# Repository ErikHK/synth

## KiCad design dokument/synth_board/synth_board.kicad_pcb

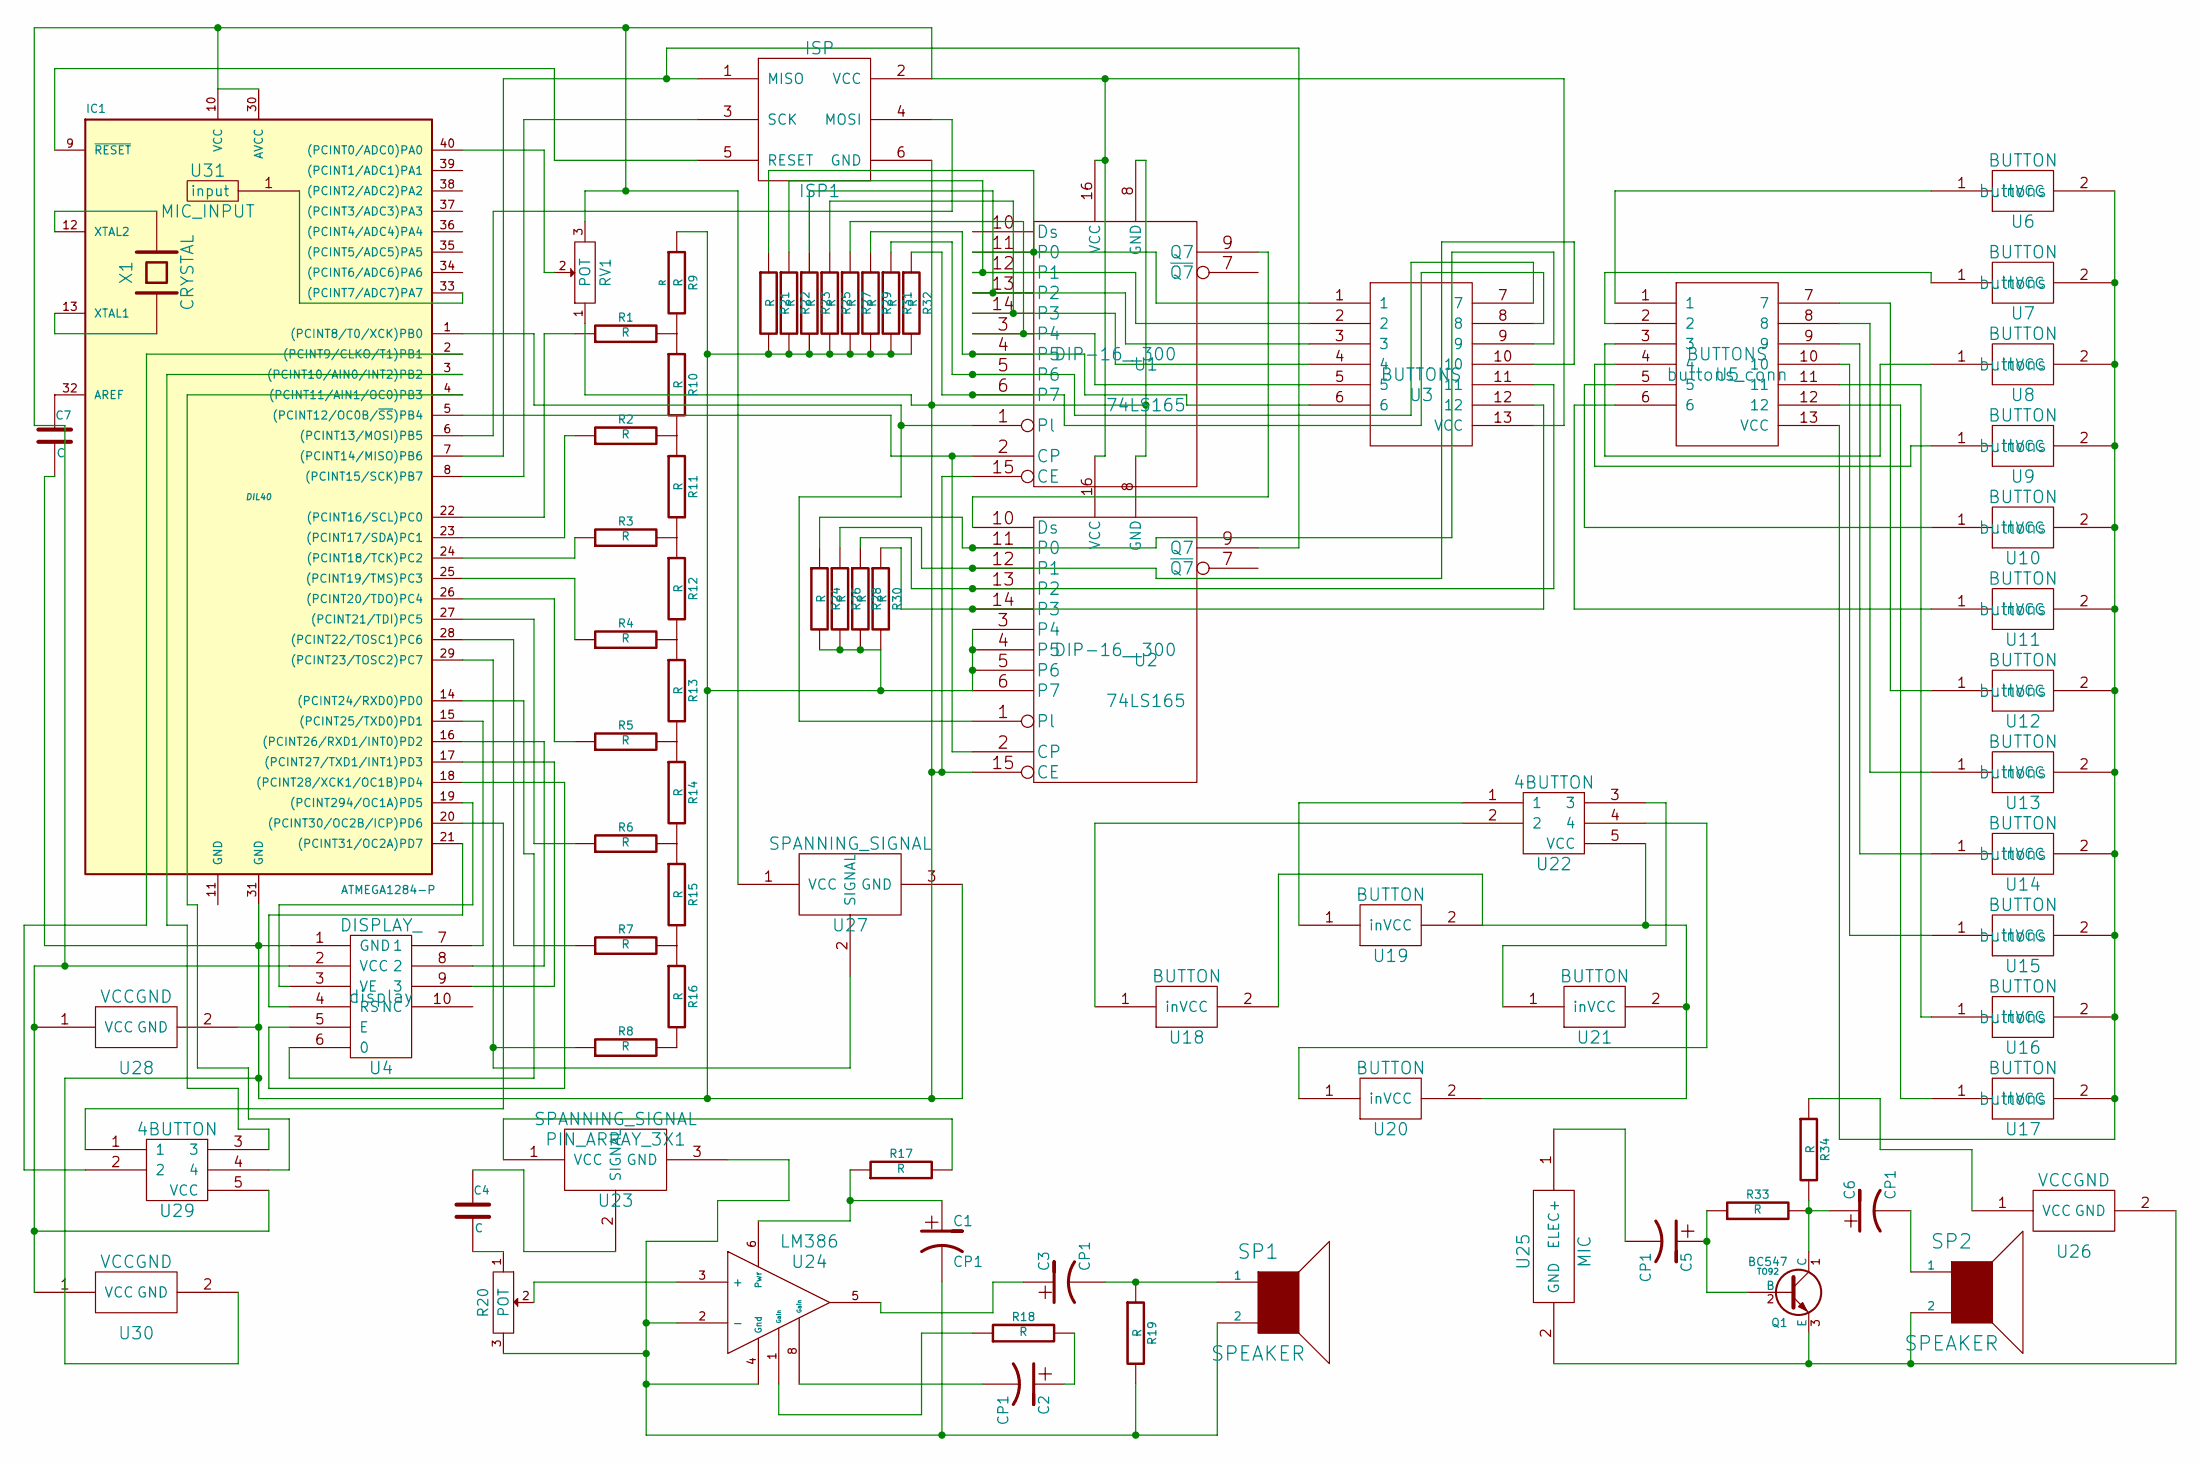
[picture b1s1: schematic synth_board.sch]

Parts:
C1, C2, C3, C5, C6: CP1
C4, C7: C
IC1: ATMEGA1284-P; DIL40
ISP1: ISP
Q1: BC547; TO92
R1, R2, R3, R4, R5, R6, R7, R8, R10, R11, R12, R13, R14, R15, R16, R17, R18, R19, R21, R22, R23, R24, R25, R26, R27, R28, R29, R30, R31, R32, R33, R34: R
R9: R
R20: POT
RV1: POT
SP1, SP2: SPEAKER
U1, U2: 74LS165; DIP-16__300
U3: BUTTONS
U4: DISPLAY_; display
U5: BUTTONS; buttons_conn
U6, U7, U8, U9, U10, U11, U12, U13, U14, U15, U16, U17: BUTTON; buttons
U18, U19, U20, U21: BUTTON
U22, U29: 4BUTTON
U23: SPANNING_SIGNAL; PIN_ARRAY_3X1
U24: LM386
U25: MIC
U26, U28, U30: VCCGND
U27: SPANNING_SIGNAL
U31: MIC_INPUT
X1: CRYSTAL

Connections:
unnamed: C4.1, U23.2 (SIGNAL)
unnamed: C4.2, R20.1
unnamed: R18.1, U24.1 (Gain)
unnamed: C2.2, U24.8 (Gain)
unnamed: C3.1, U24.5
unnamed: C2.1, R18.2
unnamed: R22.1, U1.12 (P1), U3.2
unnamed: R21.1, U1.11 (P0), U3.1
unnamed: R27.1, U1.3 (P4), U3.5
unnamed: R25.1, U1.14 (P3), U3.4
unnamed: U5.9, U14.1 (in)
unnamed: U5.5, U10.1 (in)
unnamed: U5.6, U11.1 (in)
unnamed: U5.7, U12.1 (in)
unnamed: U5.8, U13.1 (in)
unnamed: U5.10, U15.1 (in)
unnamed: U5.11, U16.1 (in)
unnamed: U5.12, U17.1 (in)
unnamed: U5.3, U8.1 (in)
unnamed: U5.2, U7.1 (in)
unnamed: U5.4, U9.1 (in)
unnamed: R20.2, U24.3 (+)
unnamed: U21.1 (in), U22.3
unnamed: C1.2, R19.2, R20.3, SP1.2, U23.3 (GND), U24.2 (-), U24.4 (Gnd)
unnamed: C1.1, R17.1, U24.6 (Pwr)
unnamed: R17.2, U23.1 (VCC)
unnamed: U19.1 (in), U22.1
unnamed: U18.1 (in), U22.2
unnamed: IC1.20 ((PCINT30/OC2B/ICP)PD6), U29.1
unnamed: IC1.13 (XTAL1), X1.1
unnamed: IC1.12 (XTAL2), X1.2
unnamed: C6.2, SP2.1
unnamed: Q1.3 (E), SP2.2, U25.2 (GND), U26.2 (GND)
unnamed: IC1.2 ((PCINT9/CLKO/T1)PB1), U29.2
unnamed: IC1.40 ((PCINT0/ADC0)PA0), RV1.2
unnamed: IC1.33 ((PCINT7/ADC7)PA7), U31.1
unnamed: IC1.3 ((PCINT10/AIN0/INT2)PB2), U29.3
unnamed: IC1.4 ((PCINT11/AIN1/OC0)PB3), U29.4
unnamed: R23.1, U1.13 (P2), U3.3
unnamed: C5.2, U25.1 (ELEC+)
unnamed: IC1.15 ((PCINT25/TXD0)PD1), U4.7 (1)
unnamed: IC1.19 ((PCINT294/OC1A)PD5), U4.3 (VE)
unnamed: U20.1 (in), U22.4
unnamed: C6.1, Q1.1 (C), R33.2, R34.2
unnamed: R34.1, U26.1 (VCC)
unnamed: IC1.21 ((PCINT31/OC2A)PD7), U4.4 (RS)
unnamed: IC1.14 ((PCINT24/RXD0)PD0), U4.6 (0)
unnamed: IC1.16 ((PCINT26/RXD1/INT0)PD2), U4.8 (2)
unnamed: IC1.17 ((PCINT27/TXD1/INT1)PD3), U4.9 (3)
unnamed: U5.1, U6.1 (in)
unnamed: IC1.5 ((PCINT12/OC0B/~SS~)PB4), U1.2 (CP), U2.2 (CP)
unnamed: R24.1, U2.11 (P0), U3.9
unnamed: R26.1, U2.12 (P1), U3.10
unnamed: R28.1, U2.13 (P2), U3.11
unnamed: R30.1, U2.14 (P3), U3.12
unnamed: U18.2 (VCC), U19.2 (VCC), U20.2 (VCC), U21.2 (VCC), U22.5 (VCC)
unnamed: U5.13 (VCC), U6.2 (VCC), U7.2 (VCC), U8.2 (VCC), U9.2 (VCC), U10.2 (VCC), U11.2 (VCC), U12.2 (VCC), U13.2 (VCC), U14.2 (VCC), U15.2 (VCC), U16.2 (VCC), U17.2 (VCC)
unnamed: R6.2, R14.2, R15.1
unnamed: R7.2, R15.2, R16.1
unnamed: R8.2, R16.2
unnamed: IC1.1 ((PCINT8/T0/XCK)PB0), U1.1 (Pl), U2.1 (Pl)
unnamed: IC1.27 ((PCINT21/TDI)PC5), R6.1
unnamed: IC1.8 ((PCINT15/SCK)PB7), ISP1.3 (SCK)
unnamed: R1.2, R9.2, R10.1
unnamed: R2.2, R10.2, R11.1
unnamed: R3.2, R11.2, R12.1
unnamed: R4.2, R12.2, R13.1
unnamed: R5.2, R13.2, R14.1
unnamed: IC1.24 ((PCINT18/TCK)PC2), R3.1
unnamed: IC1.25 ((PCINT19/TMS)PC3), R4.1
unnamed: IC1.26 ((PCINT20/TDO)PC4), R5.1
unnamed: IC1.29 ((PCINT23/TOSC2)PC7), R8.1, U27.2 (SIGNAL)
unnamed: IC1.7 ((PCINT14/MISO)PB6), ISP1.1 (MISO), U2.9 (Q7)
unnamed: IC1.9 (~RESET), ISP1.5 (RESET)
unnamed: R29.1, U1.4 (P5), U3.6
unnamed: R31.1, U1.5 (P6), U3.7
unnamed: R32.1, U1.6 (P7), U3.8
unnamed: U1.9 (Q7), U2.10 (Ds)
unnamed: IC1.22 ((PCINT16/SCL)PC0), R1.1
unnamed: C7.1, IC1.32 (AREF)
unnamed: IC1.23 ((PCINT17/SDA)PC1), R2.1
unnamed: IC1.18 ((PCINT28/XCK1/OC1B)PD4), U4.5 (E)
unnamed: IC1.28 ((PCINT22/TOSC1)PC6), R7.1
unnamed: IC1.6 ((PCINT13/MOSI)PB5), ISP1.4 (MOSI)
unnamed: C3.2, R19.1, SP1.1
unnamed: IC1.10 (VCC), IC1.30 (AVCC), ISP1.2 (VCC), RV1.3, U1.16 (VCC), U2.16 (VCC), U3.13 (VCC), U4.2 (VCC), U27.1 (VCC), U28.1 (VCC), U29.5 (VCC), U30.1 (VCC)
unnamed: C7.2, IC1.31 (GND), ISP1.6 (GND), R9.1, R21.2, R22.2, R23.2, R24.2, R25.2, R26.2, R27.2, R28.2, R29.2, R30.2, R31.2, R32.2, RV1.1, U1.8 (GND), U1.15 (CE), U2.3 (P4), U2.4 (P5), U2.5 (P6), U2.6 (P7), U2.8 (GND), U2.15 (CE), U4.1 (GND), U27.3 (GND), U28.2 (GND), U30.2 (GND)
unnamed: C5.1, Q1.2 (B), R33.1

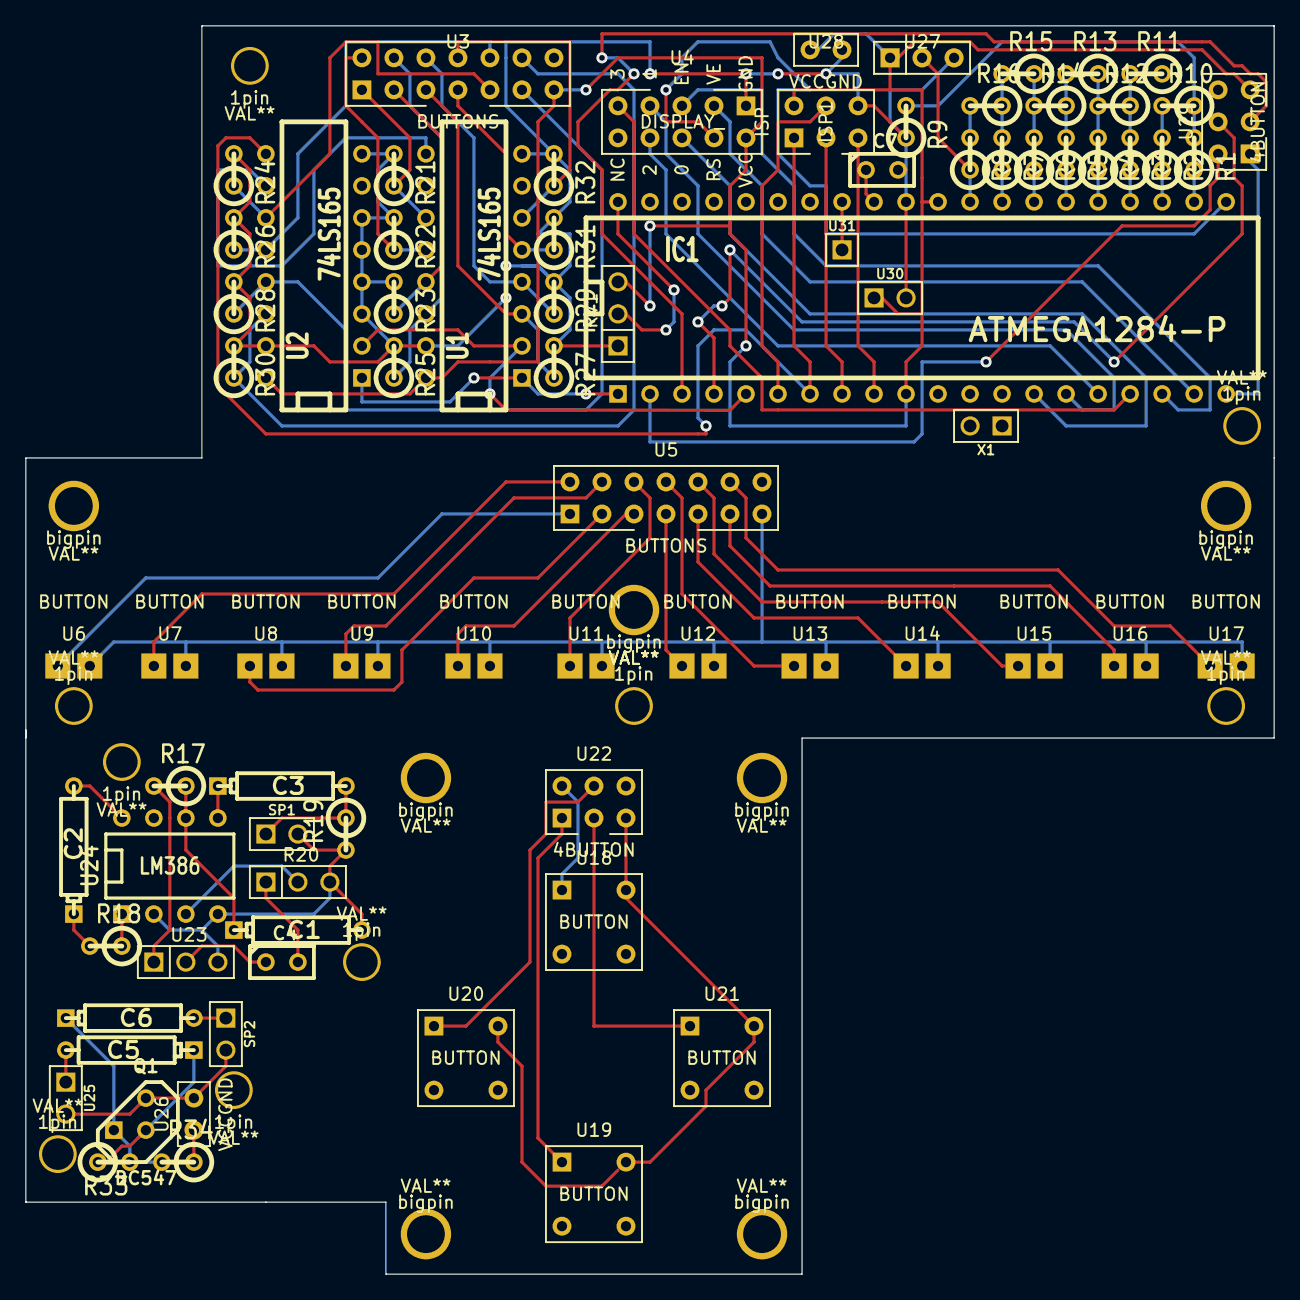
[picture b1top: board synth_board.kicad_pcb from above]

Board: 2 copper layers, 99.1 x 99.1 mm, 95 parts (0 on the bottom side), 88 nets.

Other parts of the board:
1pin, 1pin#2, 1pin#3, 1pin#4, 1pin#5, 1pin#6, 1pin#7, 1pin#8, 1pin#9: VAL**; 1pin
bigpin: VAL**; bigpin
bigpin#2, bigpin#3, bigpin#4, bigpin#5, bigpin#6, bigpin#7: VAL**; bigpin

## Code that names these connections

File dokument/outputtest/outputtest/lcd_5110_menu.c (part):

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/*
#define LCD_DDR		DDRD
#define LCD_PORT	PORTD
#define CLK			PD7
#define	DIN			PD5
#define	DC			PD4
#define CE			PD0
#define	RST			PD1
*/

#define LCD_DDR		DDRD
#define LCD_PORT	PORTD
#define CLK			PD5
#define	DIN			PD7
#define	DC			PD0
#define CE			PD4
#define	RST			PD2

#define LCD_COMMAND 0
#define LCD_DATA	1
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#define DDRLEFT		DDRD
#define PINLEFT		PIND
#define PORTLEFT	PORTD
#define LEFT		PD6

#define DDRPORT3	DDRB
#define PORT3		PORTB
#define PIN3		PINB
#define RIGHT		PB1
#define UP			PB2
#define DOWN		PB3


const uint8_t font6x8[][6] =
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
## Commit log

2013-04-22 lade till ljud och dokument
2013-04-22 lade till kod, forhoppningsvis..
2014-10-26 added lotsa shit
2014-10-26 finished routing on main board
2014-10-26 finished with main board, kind of...
2014-10-26 just going to add pot and electret mic
2014-10-26 finished yeeeey
2014-10-26 added all gerber files incl. .rar
2014-11-13 fixed things
2014-11-13 upgraded the case
2014-11-20 updated synth case
2014-11-20 added 4 buttons etc
2014-11-20 added synth case for nokia display
2014-11-20 added pot hole etc
2014-11-20 added outputtest project
2014-12-01 updated outputtest
2014-12-03 commit before cleanup
2014-12-04 added v2 case for nokia 5110 display, more room for display
2014-12-04 before clean-up of outputtest, semi-working LCD
2014-12-04 FUNGERANDE LCD, YEY
2014-12-05 fixed bottom on the new 5110 case as well
2014-12-05 fixed battery holder on the bottom case part
2014-12-05 made some white keys
2014-12-05 made the white keys bigger
2014-12-05 fixed some small bugs on the white keys
2014-12-06 working code once again
2014-12-07 added new white buttons
2014-12-07 added awesome all keys file
2014-12-07 changed awesome all keys file
2014-12-09 changed all_keys
2014-12-09 fixed foil holders for the buttons etc
2014-12-11 added potentiometer code
2014-12-11 fixed nicer keys
2014-12-17 added new thinner case, and attack/release in the code
2014-12-17 added better key_holder and inset for battery holder
2014-12-17 added inset for 4buttons and pot hole
2014-12-17 changed lcd hole size
2015-01-01 fixed buffer based and refactored code
2015-01-01 somewhat non-functioning menu system\!
2015-01-02 tracked more files
2015-01-03 start of menu system
2015-01-03 functioning menu\!
2015-01-05 added version 4 of case
2015-01-06 commenting out unnecessary things
2015-01-07 added startup logo
2015-01-10 dunno
2015-01-11 try adc values in menu
2015-01-11 better menu
2015-01-16 testing DDS, phase acc etc
2015-01-16 functioning DDS, with polyphony\!
2015-01-16 forgot to add screenshot
2015-01-20 added button mold
2015-01-20 better button_mold
2015-01-22 updated button mold etc
2015-01-23 added things to button mold
2015-01-23 first button mold test
2015-01-24 polyphony working\!
2015-01-25 loop for polyphony etc
2015-01-25 added hejhej sound to sounds.h
2015-01-25 version 2 of button mold
2015-01-29 not simple yet
2015-01-29 fixed simple\!
2015-04-01 functioning, kind of
2015-04-01 mycket battre ljud
2015-04-01 mycket battre ljud, alla knappar funkar
2016-07-27 newer v4 upper part, will work on lower now
2016-07-28 updated buttons and case
